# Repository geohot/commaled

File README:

Simple cheap USB LED Controller.

6 channel.

Want to buy it on kickstarter?

Actually I want the Chinese to clone this. Then I can buy it on amazon.

I'm too old to solder shit.

Oh Cypress why is your windows software. Linux command line no IDE plz.

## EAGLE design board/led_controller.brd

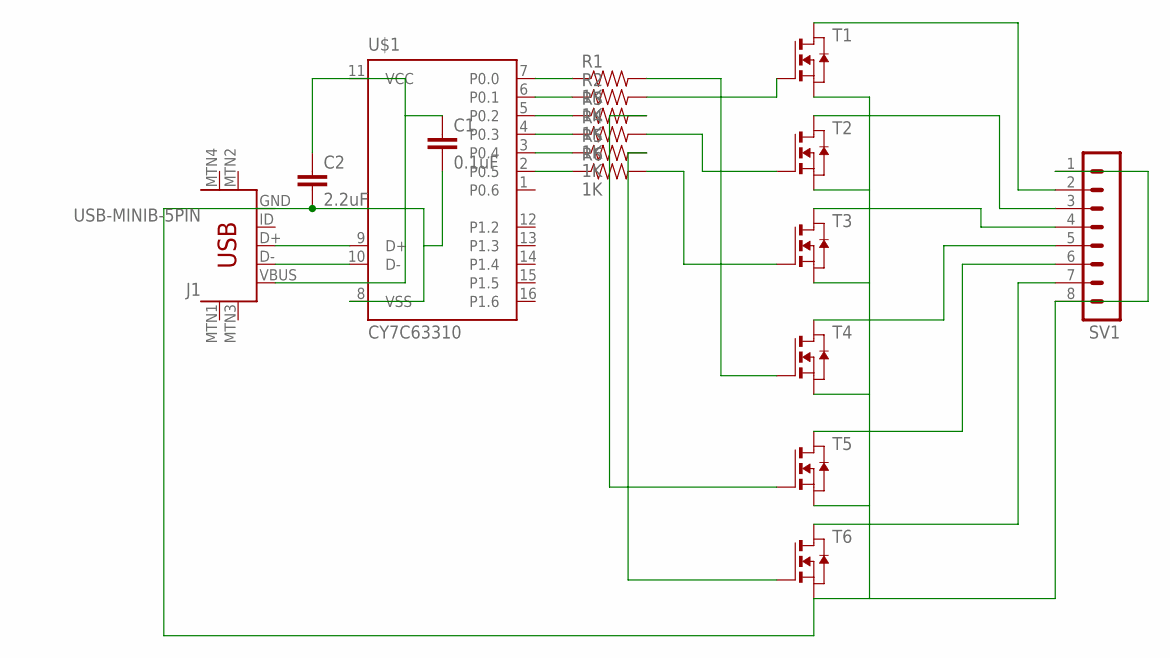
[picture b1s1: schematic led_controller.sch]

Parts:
C1: 0.1uF; 0603-CAP
C2: 2.2uF; 0805-CAP
J1: USB-MINIB-5PIN; USB-MINIB
R1, R2, R3, R4, R5, R6: 1K; 0603-RES
SV1: MA08-1
T1, T2, T3, T4, T5, T6: NMOSSOT223; SOT223
U$1: CY7C63310; SOIC16

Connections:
unnamed: J1.D+, U$1.9 (D+)
unnamed: J1.D-, U$1.10 (D-)
unnamed: C1.1, C2.1, J1.VBUS, U$1.11 (VCC)
unnamed: C1.2, C2.2, J1.GND, SV1.1, SV1.8, T1.3 (S), T2.3 (S), T3.3 (S), T4.3 (S), T5.3 (S), T6.3 (S), U$1.8 (VSS)
unnamed: R6.1, U$1.2 (P0.5)
unnamed: R5.1, U$1.3 (P0.4)
unnamed: R4.1, U$1.4 (P0.3)
unnamed: R3.1, U$1.5 (P0.2)
unnamed: R2.1, U$1.6 (P0.1)
unnamed: R1.1, U$1.7 (P0.0)
unnamed: R6.2, T3.1 (G)
unnamed: R5.2, T6.1 (G)
unnamed: R4.2, T2.1 (G)
unnamed: R3.2, T5.1 (G)
unnamed: R2.2, T1.1 (G)
unnamed: R1.2, T4.1 (G)
unnamed: SV1.2, T1.2 (D), T1.4 (D)
unnamed: SV1.3, T2.2 (D), T2.4 (D)
unnamed: SV1.4, T3.2 (D), T3.4 (D)
unnamed: SV1.5, T4.2 (D), T4.4 (D)
unnamed: SV1.6, T5.2 (D), T5.4 (D)
unnamed: SV1.7, T6.2 (D), T6.4 (D)

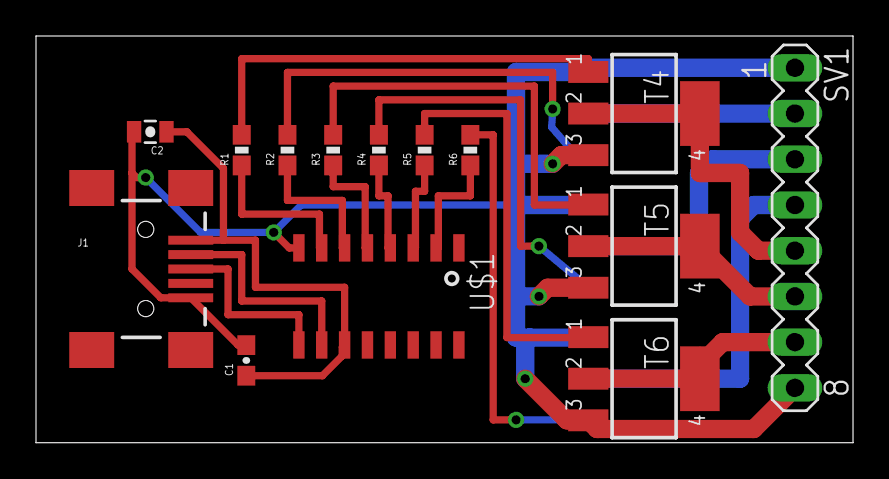
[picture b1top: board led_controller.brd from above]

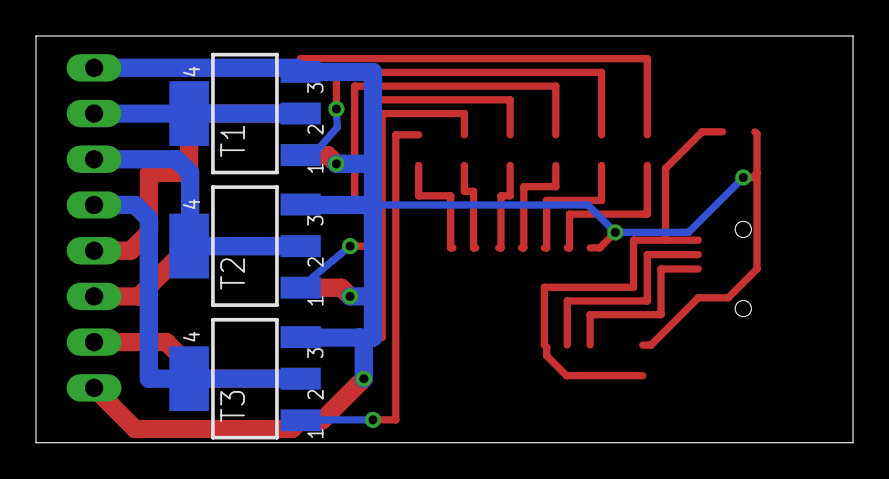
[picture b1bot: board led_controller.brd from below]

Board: 2 copper layers, 45.4 x 22.6 mm, 17 parts (3 on the bottom side), 22 nets.

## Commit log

2015-12-07 working
2015-12-07 maximum swag
2015-12-07 oh of course 27 things change
2015-12-07 get faded
2015-12-07 only file that matters
2015-12-07 upgraded readme
2015-12-07 better
2015-12-07 ALL 6 CHANNELS
2015-12-12 turn off on exit
2015-12-16 Any particular reason for using 37.7833,-122.4167 for the coordinates? I thought I saw an Acura ILX on the street view.

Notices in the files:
parts and their libraries:
SparkFun-Capacitors: Licensing: Creative Commons ShareAlike 4.0 International - https://creativecommons.org/licenses/by-sa/4.0
